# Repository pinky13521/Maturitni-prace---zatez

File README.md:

# ⚡ Programovatelná stejnosměrná elektronická zátěž (0–30 V / 0–5 A / 65 W)

-green?style=flat-square&logo=kicad)

**Maturitní projekt** na SPŠ elektrotechnické zaměřený na návrh, konstrukci a programové vybavení číslicově řízené laboratorní stejnosměrné elektronické zátěže. Zařízení slouží k testování charakteristik napájecích zdrojů, ověřování proudové zatížitelnosti adaptérů a automatizovanému měření kapacity i vnitřního odporu akumulátorů.

---

## 🎯 Hlavní technické parametry

| Parametr | Hodnota / Rozsah | Poznámka |
| :--- | :--- | :--- |
| **Vstupní napětí ($U_{\text{in}}$)** | **0 – 30 V DC** | Havarijní přepěťová ochrana OVP při 32,0 V (kritická 34,0 V) |
| **Zatěžovací proud ($I_{\text{load}}$)** | **0 – 5,0 A** | Nadproudová ochrana OCP při 5,20 A |
| **Maximální ztrátový výkon ($P_{\text{max}}$)** | **65 W trvale** (100 W špičkově) | Aktivní chlazení CPU chladičem s heatpipes + softwarový derating |
| **Rozlišení nastavení proudu (DAC)** | **~1,22 mA / LSB** | Externí 12-bitový I2C D/A převodník **MCP4725** |
| **Rozlišení měření (ADC)** | **1,38 mV / 1,25 mA** | Externí 16-bitový Sigma-Delta A/D převodník **ADS1115** (860 SPS) |
| **Provozní režimy** | **CC, CP, CR, BATT** | Konstantní proud, výkon, odpor a automatický test baterií |
| **Regulační smyčka** | **Analogová + 50 Hz digitální** | Plynulý soft-start náběh proudu (17,5 A/s) bez rázů |
| **Ovládání a rozhraní** | **OLED + Enkodér + Wi-Fi Web** | Lokální 0,96" OLED displej, rotační enkodér s akcelerací, Web HUD |

---

## 🛠️ Hybridní architektura systému

Zařízení využívá **hybridní analogově-digitální koncepci**, která spojuje bleskovou odezvu analogového regulátoru s přesností a inteligencí mikrokontroléru ESP32:

```mermaid
flowchart LR
    subgraph Power["Výkonová a analogová část"]
        DUT["Testovaný zdroj / Baterie\n(0–30 V / 0–5 A)"] --> Q1["IRFP250N\n(TO-247 MOSFET)"]
        Q1 --> RSH["Bočník 0,100 Ω / 10 W\n(4-vodičové Kelvinovo snímání)"]
        RSH --> GND["GND"]
        DAC["MCP4725\n(12-bit DAC)"] --> OA["LM358\n(Operační zesilovač)"]
        RSH -. "Zpětná vazba IMON" .-> OA
        OA -- "Buzení Gate" --> Q1
    end

    subgraph Digital["Číslicové řízení a telemetrie (ESP32)"]
        ADC["ADS1115\n(16-bit ADC)"] --> ESP["ESP32 DevKit V1\n(240 MHz Dual-Core)"]
        DUT -. "Dělič 1:11 (VMON)" .-> ADC
        RSH -. "Úbytek (IMON)" .-> ADC
        TEMP["DS18B20\n(Teplota chladiče)"] --> ESP
        ENC["Rotační enkodér\nKY-040"] --> ESP
        ESP --> DAC
        ESP -- "25 kHz PWM" --> FAN["4-pin PC Ventilátor"]
        ESP --> OLED["0.96\" SSD1306 OLED"]
        ESP <--> WEB["Wi-Fi Webové Rozhraní\n(http://zatez.local)"]
    end
```

1. **Rychlá analogová proudová smyčka**: Operační zesilovač **LM358** plynule porovnává žádané napětí z D/A převodníku s okamžitým úbytkem napětí na výkonovém bočníku **0,100 Ω / 10 W** a řídí hradlo výkonového N-MOSFETu **IRFP250N** v lineárním režimu. Analogová smyčka reaguje v řádu mikrosekund a potlačuje proudové špičky při připojení zátěže.
2. **Číslicový dohled a regulace (ESP32)**: Mikrokontrolér v deterministické 50Hz smyčce (perioda 20 ms) čte skutečné svorkové napětí a proud pomocí 16-bitového **ADS1115**, přepočítává požadovaný proud pro režimy **CP** ($I = P/U$), **CR** ($I = U/R$) a **BATT**, integruje kapacitu ($\text{mAh}, \text{Wh}$) a dohlíží na bezpečnostní limity.

---

## 💻 Webové rozhraní (Web Dashboard HUD)

Webová aplikace běží přímo z paměti PROGMEM mikrokontroléru ESP32 (dostupná v lokální síti přes mDNS na adrese `http://zatez.local` nebo v záložním AP režimu `ESP32-Elektronicka-Zatez`).

### Klíčové funkce webového rozhraní:
* **☰ Vysouvací postranní panel (GitHub-style Drawer Menu)**: Kliknutím na ikonu tří čárek `☰` v levém horním rohu se vysune přehledné navigační menu rozdělené do sekcí (*Provoz a měření*, *Konfigurace a systém*, *Vzhled a rozhraní*) včetně živého mini-přehledu veličin a rychlého přepínače motivů.
* **📊 4 barevně kódované digitální přístroje**:
  * ⚡ **Napětí ($U$)**: Ledově modrá (`0.00 V`)
  * 🟢 **Proud ($I$)**: Smaragdově zelená (`0.000 A`)
  * 🟡 **Výkon ($P$)**: Jantarově zlatá (`0.0 W`)
  * 🔴 **Teplota & Ventilátor ($T$)**: Korálově červená (`25.0 °C // 20%`)
* **📈 Retina HiDPI osciloskop**: Vykreslování průběhu napětí a proudu v reálném čase s automatickým škálováním podle `window.devicePixelRatio`, volbou délky paměti (`50 / 100 / 150` bodů) a přepínáním **lineárního (LIN)** i **logaritmického (LOG)** měřítka osy Y i posuvníku.
* **🔋 Analyzátor kapacity baterií**:
  * Přesné měření vybíjecí kapacity v **mAh / Ah** a energie ve **Wh** (64-bitová integrace).
  * Automatický výpočet **vnitřního odporu článku ($R_i$)** v $\text{m}\Omega$ metodou poklesu napětí při zatížení ($R_i = \Delta U / \Delta I$).
  * Rychlé předvolby pro **Li-Ion / LiPo (3,0 V)**, **LiFePO4 (2,5 V)**, **NiMH (1,0 V)** a **Pb 12V (10,5 V)** s automatickým odpojením při dosažení mezního napětí (Cut-off).
* **📥 Záznamník dat (Data Logger) a export**:
  * Záznam průběhu měření do paměti s přímým exportem do **Excelu (`.csv` s UTF-8 BOM a českým formátem desetinné čárky)**, surového **`.json`** a uložením snímku grafu jako **`.png` obrázku**.
* **🎨 5 laboratorních barevných motivů & lokalizace**:
  * *Cyber Dark*, *Keithley Amber*, *CRT Phosphor Green*, *Neon Cyan* a *Clean Paper Light* (světlý režim pro tisk do protokolů).
  * Okamžité přepínání jazyka **Čeština (CZ) / English (EN)** a zvuková odezva tlačítek i alarmů přes **Web Audio API**.

---

## ⚡ Optimalizace firmwaru (v2.5 Optimized Pro)

1. **Ne-blokující asynchronní stavový automat ADC (`adc_driver.cpp`)**:
   * Odstraněno blokující čekání na I2C převody. Stavový automat `poll()` spouští převody na pozadí (860 SPS) a střídá kanály napětí a proudu. Samotné čtení v regulační smyčce trvá **0 µs**.
2. **Plynulý Soft-Start náběh proudu (`dac_driver.cpp`)**:
   * Implementován omezovač strmosti náběhu (*slew-rate limiter* max. $+0{,}35\,\text{A} / 20\,\text{ms} = 17{,}5\,\text{A/s}$), který chrání testovaný zdroj i MOSFET před proudovými rázy a překmity. Vypnutí zátěže zůstává okamžité.
3. **Dynamická akcelerace rotačního enkodéru (`encoder_driver.cpp`)**:
   * Přerušovací rutina měří rychlost otáčení knoflíku ($\Delta t$ v $\mu\text{s}$). Při pomalém otáčení umožňuje jemné krokování po 50 mA ($1\times$), při rychlém protočení násobí krok ($2\times$ až $3\times$).
4. **64-bitová integrace kapacity (`load_regulator.cpp`)**:
   * Vnitřní akumulátory mAh a Wh využívají 64-bitový typ `double`, čímž eliminují zaokrouhlovací chybu plovoucí řádové čárky při dlouhodobých vícehodinových testech baterií.
5. **Odolnost bezpečnostních ochran proti šumu (`safety.cpp`)**:
   * Čtyřstupňový **Safety Supervisor** (**OVP** 32 V, **OCP** 5,2 A, **OPP** 65 W, **OTP** 75 °C) využívá persistenciální filtr (potvrzení 2–3 po sobě jdoucích vzorků za 40–60 ms) proti falešným sepnutím vlivem rušení, zatímco při kritickém přepětí ($>34\,\text{V}$) odpojuje zátěž okamžitě.
6. **Optimalizace Flash paměti (`min_spiffs.csv` + `-O2`)**:
   * Úpravou rozvržení partition tabulky a kompilační optimalizací `-O2` bylo využití paměti Flash sníženo z 94 % na **56,8 %**.

---

## 📌 Přiřazení pinů ESP32 (Pinout dle schématu v KiCadu)

| Periferie / Signál | Pin ESP32 (GPIO) | Konektor na DPS | Popis funkce |
| :--- | :--- | :--- | :--- |
| **I2C SDA** | `GPIO 26` | `J_ESP_R1` (pin 7) | Datová linka I2C (400 kHz Fast Mode – OLED, ADS1115, MCP4725) |
| **I2C SCL** | `GPIO 14` | `J_ESP_R1` (pin 5) | Hodinová linka I2C (400 kHz) |
| **1-Wire DS18B20** | `GPIO 32` | `J_ESP_R1` (pin 10) | Digitální teploměr chladiče Dallas DS18B20 (4,7 kΩ pull-up) |
| **PWM Ventilátor** | `GPIO 33` | `J_ESP_R1` (pin 9) | 25 kHz PWM řízení otáček 4-pinového PC ventilátoru (20–100 %) |
| **Enkodér CLK** | `GPIO 18` | `J_ESP_L1` (pin 9) | Externí přerušení rotačního enkodéru (kanál A) |
| **Enkodér DT** | `GPIO 19` | `J_ESP_L1` (pin 10) | Směrový signál rotačního enkodéru (kanál B) |
| **Enkodér SW** | `GPIO 21` | `J_ESP_L1` (pin 11) | Tlačítko enkodéru (krátký stisk = ZAP/VYP, dlouhý stisk = změna režimu) |

---

## 📁 Struktura repozitáře

```text
├── hardware/                  # Kompletní návrh DPS a schématu v KiCad 9.0
│   ├── elektronicka zatez.kicad_pro
│   ├── elektronicka zatez.kicad_sch   # Elektrické schéma (32 součástek, plně propojeno)
│   └── elektronicka zatez.kicad_pcb   # Dvouvrstvá DPS (DRC: 0 chyb, 0 nepřipojených spojů)
├── firmware/                  # Zdrojový kód pro ESP32 (PlatformIO / Arduino C++)
│   ├── platformio.ini         # Konfigurace sestavení, knihoven a partition tabulky
│   ├── include/
│   │   ├── config.h           # Konfigurace pinů, kalibrace, Wi-Fi a bezpečnostních limitů
│   │   ├── types.h            # Datové struktury a výčtové typy
│   │   ├── hal/               # Ovladače hardwaru (ADC, DAC, Ventilátor, Teploměr, Enkodér)
│   │   ├── core/              # Regulační smyčka (CC/CP/CR/BATT) a Safety Supervisor
│   │   ├── ui/                # Vykreslování na 0,96" OLED displej SSD1306
│   │   └── net/               # Wi-Fi manažer, REST API server a Web Dashboard (PROGMEM)
│   └── src/                   # Implementační soubory (.cpp) a hlavní smyčka main.cpp
└── docs/                      # Technická dokumentace a kusovník (BOM)
```

---

## 🚀 Kompilace a nahrání firmwaru

1. Otevřete složku `firmware/` ve vývojovém prostředí **VS Code** s rozšířením **PlatformIO**.
2. V souboru [`firmware/include/config.h`](firmware/include/config.h) můžete upravit přihlašovací údaje k domácí Wi-Fi síti (`WIFI_STA_SSID` a `WIFI_STA_PASS`). Pokud se zátěž k routeru nepřipojí, automaticky vytvoří vlastní přístupový bod **`ESP32-Elektronicka-Zatez`** (heslo `12345678`, IP `192.168.4.1`).
3. Zkompilujte a nahrajte projekt příkazem:
   ```bash
   pio run -t upload -d firmware
   ```
4. Otevřete webové rozhraní v prohlížeči na adrese **`http://zatez.local`** (nebo na IP adrese vypsané na OLED displeji při startu).

---
*Autor projektu: **Ondřej Pinkas** — Maturitní práce, SPŠ Elektrotechnická*

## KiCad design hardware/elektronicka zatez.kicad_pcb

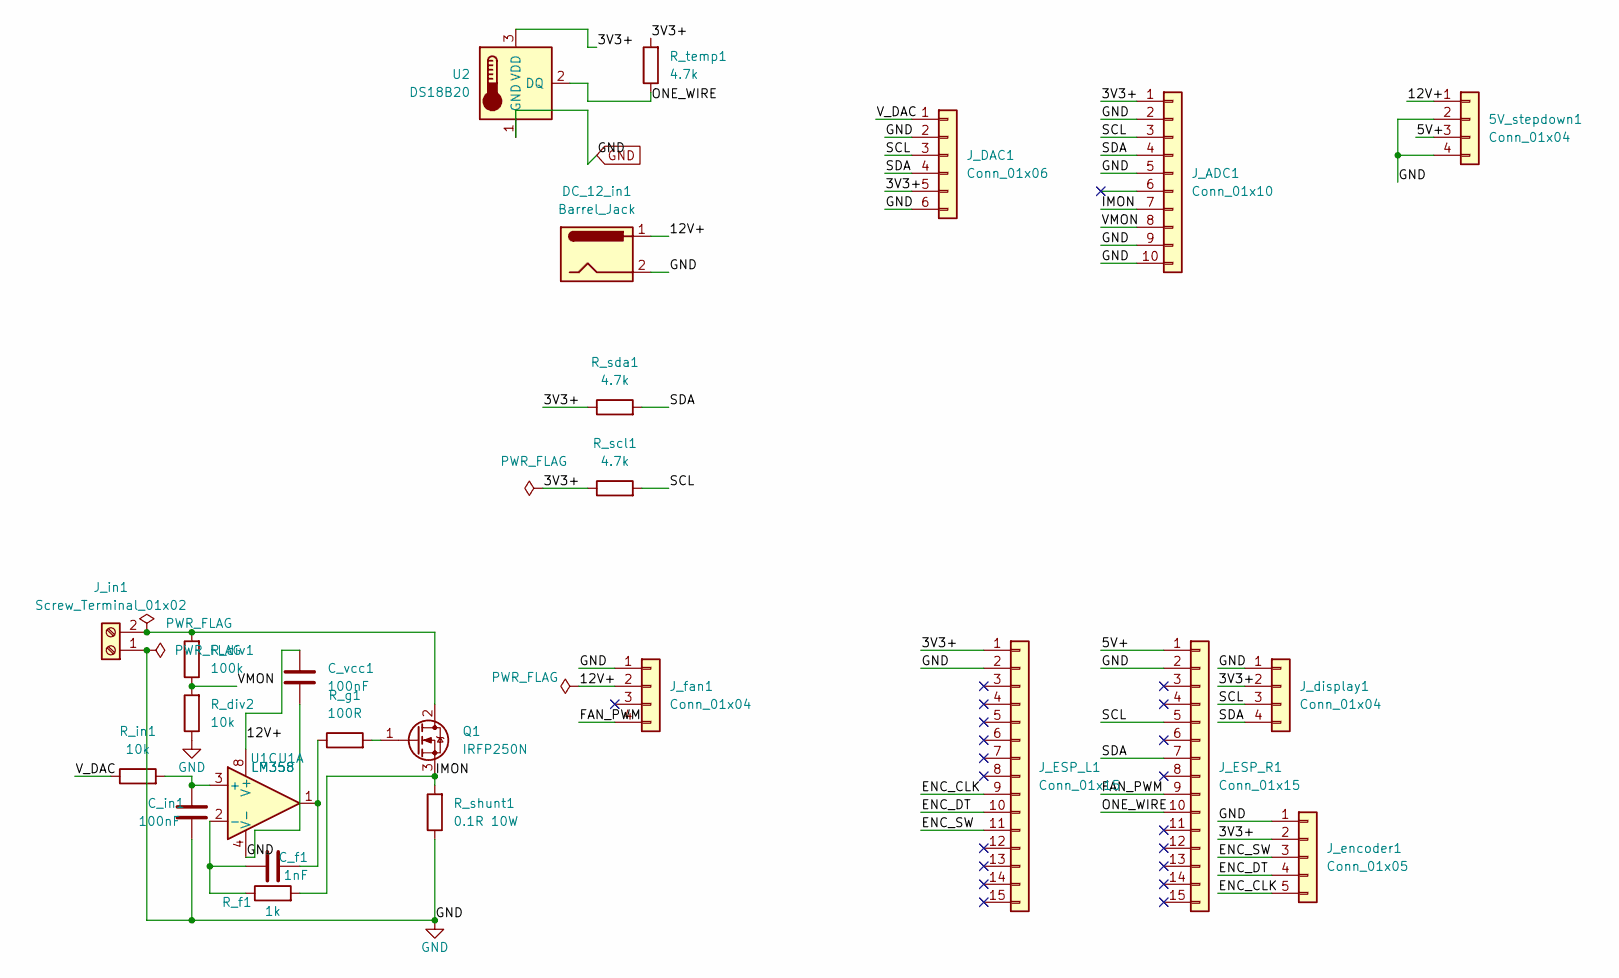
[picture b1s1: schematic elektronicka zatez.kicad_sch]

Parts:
5V_stepdown1: Conn_01x04; PinHeader_1x04_P2.54mm_Vertical
C_f1: 1nF; C_Disc_D5.0mm_W2.5mm_P5.00mm
C_in1: 100nF; C_Disc_D5.0mm_W2.5mm_P5.00mm
C_vcc1: 100nF; C_Disc_D5.0mm_W2.5mm_P5.00mm
DC_12_in1: Barrel_Jack; BarrelJack_CUI_PJ-063AH_Horizontal
J_ADC1: Conn_01x10; PinSocket_1x10_P2.54mm_Vertical
J_DAC1: Conn_01x06; PinSocket_1x06_P2.54mm_Vertical
J_ESP_L1: Conn_01x15; PinSocket_1x15_P2.54mm_Vertical
J_ESP_R1: Conn_01x15; PinSocket_1x15_P2.54mm_Vertical
J_display1: Conn_01x04; PinSocket_1x04_P2.54mm_Vertical
J_encoder1: Conn_01x05; PinHeader_1x05_P2.54mm_Vertical
J_fan1: Conn_01x04; PinSocket_1x04_P2.54mm_Vertical
J_in1: Screw_Terminal_01x02; TerminalBlock_Phoenix_MKDS-1,5-2-5.08_1x02_P5.08mm_Horizont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
Q1: IRFP250N; TO-247-3_Vertical
R_div1: 100k; R_Axial_DIN0207_L6.3mm_D2.5mm_P10.16mm_Horizontal
R_div2: 10k; R_Axial_DIN0207_L6.3mm_D2.5mm_P10.16mm_Horizontal
R_f1: 1k; R_Axial_DIN0207_L6.3mm_D2.5mm_P10.16mm_Horizontal
R_g1: 100R; R_Axial_DIN0207_L6.3mm_D2.5mm_P10.16mm_Horizontal
R_in1: 10k; R_Axial_DIN0207_L6.3mm_D2.5mm_P10.16mm_Horizontal
R_scl1: 4.7k; R_Axial_DIN0207_L6.3mm_D2.5mm_P10.16mm_Horizontal
R_sda1: 4.7k; R_Axial_DIN0207_L6.3mm_D2.5mm_P10.16mm_Horizontal
R_shunt1: 0.1R 10W; R_Axial_Power_L50.0mm_W9.0mm_P55.88mm
R_temp1: 4.7k; R_Axial_DIN0207_L6.3mm_D2.5mm_P10.16mm_Horizontal
U1: LM358; DIP-8_W7.62mm
U2: DS18B20; TO-92_Inline

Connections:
/3V3+: J_ADC1.1, J_DAC1.5, J_ESP_L1.1, J_display1.2, J_encoder1.2, R_scl1.1, R_sda1.1, R_temp1.2, U2.3 (VDD); also elsewhere on the board
/5V+: 5V_stepdown1.3, J_ESP_R1.1
/12V+: 5V_stepdown1.1, C_vcc1.1, DC_12_in1.1, J_fan1.2, U1.8 (V+)
/ENC_CLK: J_ESP_L1.9, J_encoder1.5
/ENC_DT: J_ESP_L1.10, J_encoder1.4
/ENC_SW: J_ESP_L1.11, J_encoder1.3
/FAN_PWM: J_ESP_R1.9, J_fan1.4
/IMON: J_ADC1.7, Q1.3 (S), R_f1.2, R_shunt1.2
/ONE_WIRE: J_ESP_R1.10, R_temp1.1, U2.2 (DQ); also elsewhere on the board
/SCL: J_ADC1.3, J_DAC1.3, J_ESP_R1.5, J_display1.3, R_scl1.2
/SDA: J_ADC1.4, J_DAC1.4, J_ESP_R1.7, J_display1.4, R_sda1.2
/VMON: J_ADC1.8, R_div1.1, R_div2.2
/V_DAC: J_DAC1.1, R_in1.1
GND: 5V_stepdown1.2, 5V_stepdown1.4, C_in1.2, C_vcc1.2, DC_12_in1.2, J_ADC1.2, J_ADC1.5, J_ADC1.9, J_ADC1.10, J_DAC1.2, J_DAC1.6, J_ESP_L1.2, J_ESP_R1.2, J_display1.1, J_encoder1.1, J_fan1.1, J_in1.1, R_div2.1, R_shunt1.1, U1.4 (V-), U2.1 (GND); also elsewhere on the board
unnamed: C_f1.1, R_g1.1, U1.1
unnamed: C_f1.2, R_f1.1, U1.2 (-)
unnamed: C_in1.1, R_in1.2, U1.3 (+)
unnamed: J_in1.2, Q1.2 (D), R_div1.2
unnamed: Q1.1 (G), R_g1.2

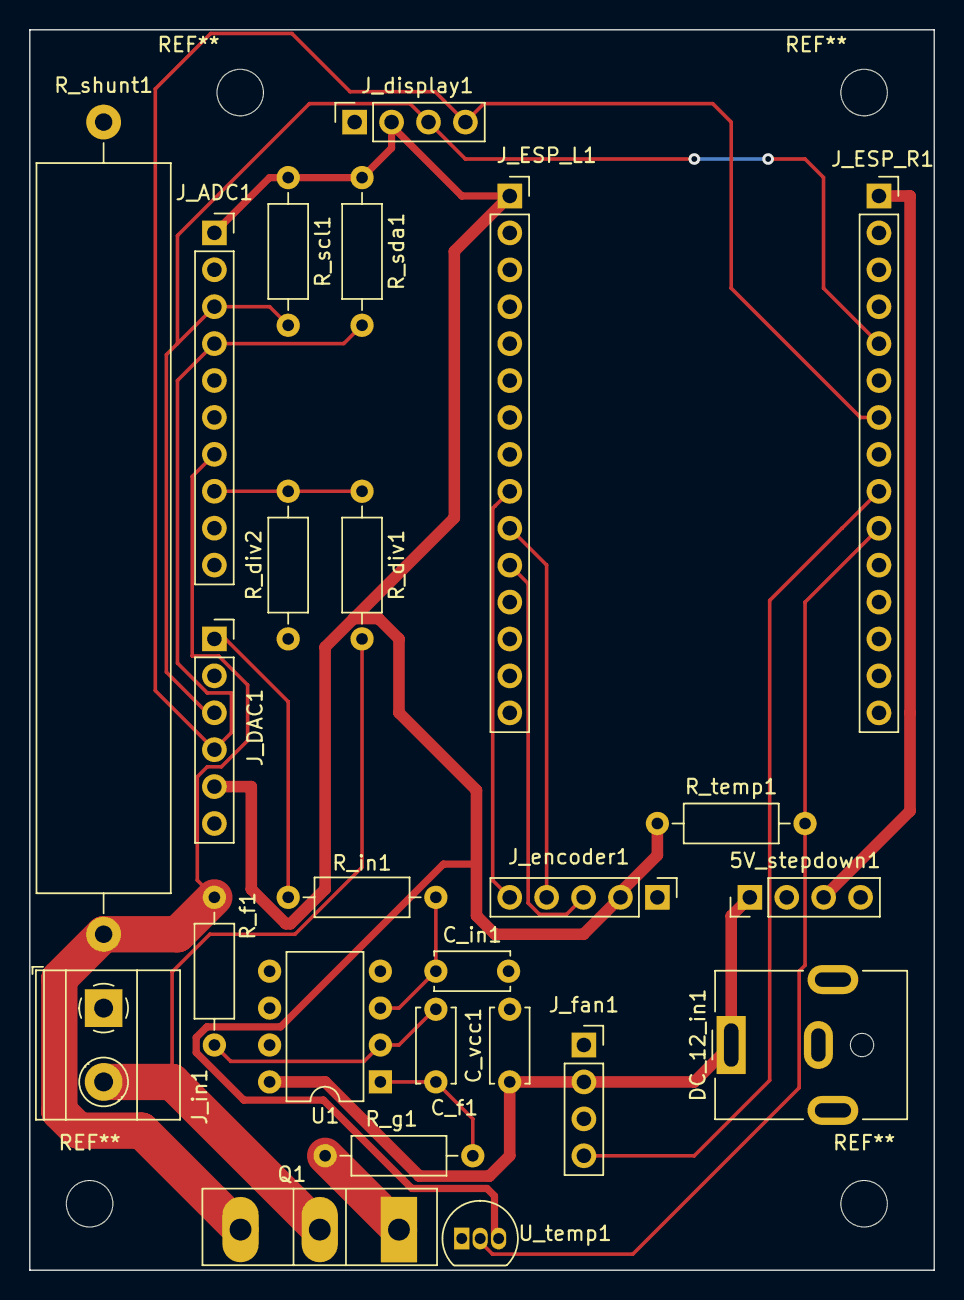
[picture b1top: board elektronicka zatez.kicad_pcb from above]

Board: 2 copper layers, 62.2 x 85.3 mm, 25 parts (0 on the bottom side), 19 nets.

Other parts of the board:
U_temp1: DS18B20; TO-92_Inline

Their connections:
/3V3+: U_temp1.3 (VDD); also elsewhere on the board
/ONE_WIRE: U_temp1.2 (DQ); also elsewhere on the board
GND: U_temp1.1 (GND); also elsewhere on the board

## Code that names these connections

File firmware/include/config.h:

/**
 * @file config.h
 * @brief Konfigurace pinů, kalibračních konstant a bezpečnostních limitů
 * @project Programovatelná stejnosměrná elektronická zátěž
 * @author Ondřej Pinkas
 */

#ifndef CONFIG_H
#define CONFIG_H

#include <Arduino.h>

// =============================================================================
// 1. PŘIŘAZENÍ PINŮ (Dle KiCad schématu pro ESP32 DevKit V1 30-pin)
// =============================================================================

// I2C Sběrnice (OLED 128x64, ADS1115, MCP4725) - ESP32 USB-C konektorem nahoru
#define PIN_I2C_SDA 26  // J_ESP_R1 pin 7 (GPIO26 / D26)
#define PIN_I2C_SCL 14  // J_ESP_R1 pin 5 (GPIO14 / D14)
#define I2C_FREQ 400000 // 400 kHz (Fast Mode)

// I2C Adresy modulů
#define I2C_ADDR_OLED 0x3C    // Výchozí adresa 0.96" SSD1306 displeje
#define I2C_ADDR_ADS1115 0x48 // Výchozí adresa 16-bit ADC (ADDR -> GND)
#define I2C_ADDR_MCP4725 0x60 // Výchozí adresa 12-bit DAC (A0 -> GND)

// Kanály ADS1115 (Dle KiCad schématu: J_ADC1 pin 7 = A0 -> IMON, pin 8 = A1 ->
// VMON)
#define ADC_CHANNEL_IMON 0 // Kanál A0: Snímání proudu bočníkem (IMON)
#define ADC_CHANNEL_VMON 1 // Kanál A1: Snímání napětí děličem (VMON)

// Rotační enkodér s tlačítkem
#define PIN_ENC_CLK 18 // J_ESP_L1 pin 9 (GPIO18 / D18)
#define PIN_ENC_DT 19  // J_ESP_L1 pin 10 (GPIO19 / D19)
#define PIN_ENC_SW 21  // J_ESP_L1 pin 11 (GPIO21 / D21)

// PWM řízení 4pinového ventilátoru
#define PIN_FAN_PWM 33     // J_ESP_R1 pin 9 (GPIO33 / D33)
#define FAN_PWM_CHANNEL 0  // LEDC kanál (pro Core 2.x)
#define FAN_PWM_FREQ 25000 // 25 kHz (standard pro 4-pin PC ventilátory)
#define FAN_PWM_RES 8      // 8-bitové rozlišení (0 až 255)

// 1-Wire sběrnice pro teplotní senzor Dallas DS18B20
#define PIN_ONE_WIRE 32 // J_ESP_R1 pin 10 (GPIO32 / D32)

#define SERIAL_DEBUG 1 // 1 = ladicí výpisy do Serial monitoru, 0 = vypnuto

#if SERIAL_DEBUG
#define LOG_PRINTLN(x) Serial.println(x)
#define LOG_PRINTF(...) Serial.printf(__VA_ARGS__)
#define LOG_PRINT(x) Serial.print(x)
#else
#define LOG_PRINTLN(x)
#define LOG_PRINTF(...)
#define LOG_PRINT(x)
#endif

// =============================================================================
// 2. HARDWAROVÉ A KALIBRAČNÍ KONSTANTY
// =============================================================================

// Proudový bočník (R_shunt1 = 0.1 Ohm / 10W Kelvinovo čtyřvodičové zapojení)
#define SHUNT_RESISTANCE_OHM 0.100f

// Napěťový dělič vstupu (R_div1 = 100k, R_div2 = 10k) => poměr (100+10)/10
// = 11.0
#define VOLTAGE_DIVIDER_RATIO 11.00f

// D/A Převodník MCP4725 (12-bit: 0..4095)
#define DAC_VREF_VOLTS 3.300f // Skutečná napájecí větev 3.3V
#define DAC_MAX_VALUE 4095

// =============================================================================
// 3. BEZPEČNOSTNÍ LIMITY (SAFETY SUPERVISOR)
// =============================================================================

#define LIMIT_MAX_VOLTAGE 32.0f // [V] OVP - Přepěťová ochrana
#define LIMIT_MAX_CURRENT 5.2f  // [A] OCP - Nadproudová ochrana
#define LIMIT_MAX_POWER 65.0f   // [W] OPP - Maximální ztrátový výkon
#define LIMIT_MAX_TEMP 75.0f    // [°C] OTP - Havarijní vypnutí zátěže
#define LIMIT_WARN_TEMP 65.0f   // [°C] Výstražná teplota (ventilátor 100%)

// Křivka ventilátoru
#define TEMP_FAN_MIN 32.0f // [°C] Pod touto teplotou minimální otáčky (20%)
#define TEMP_FAN_MAX 60.0f // [°C] Nad touto teplotou plné otáčky (100%)

// =============================================================================
// 4. WI-FI A WEBOVÝ SERVER
// =============================================================================

// Režim Klienta (STA) - ESP32 se připojí k vaší domácí / školní Wi-Fi síti nebo
// hotspotu. Skutečné údaje uložte do souboru include/secrets.h (viz secrets.h.example),
// který je v .gitignore a nenahrává se na GitHub:
#if __has_include("secrets.h")
  #include "secrets.h"
#else
  #define WIFI_STA_SSID "Vase-WiFi-Nazev"  // Zadejte název své Wi-Fi sítě
  #define WIFI_STA_PASS "Vase-WiFi-Heslo"  // Zadejte heslo k Wi-Fi
#endif
#define WIFI_STA_TIMEOUT_MS 9000 // Časový limit pro připojení k routeru [ms]

// Záložní režim Access Point (AP) - Spustí se automaticky, pokud se nepodaří
// připojit k STA:
#define WIFI_AP_SSID "ESP32-Elektronicka-Zatez"
#define WIFI_AP_PASS "12345678"
#define WEB_SERVER_PORT 80

// Lokální mDNS adresa - V prohlížeči otevřete přímo: http://zatez.local
#define MDNS_HOSTNAME "zatez"

// =============================================================================
// 5. MQTT PROPOJENÍ S LOKÁLNÍM SERVEREM (VOLITELNÉ)
// =============================================================================
// Přepněte na 1, jakmile rozchodíte Mosquitto broker na vašem serveru.
// Při 0 běží pouze vestavěný lokální webový server na ESP32.
#define MQTT_ENABLED             0
#define MQTT_BROKER_IP           "192.168.31.251"
#define MQTT_BROKER_PORT         1883
#define MQTT_CLIENT_ID           "esp32-zatez"
#define MQTT_PUBLISH_INTERVAL_MS 200
#define MQTT_TOPIC_TELEMETRY     "zatez/telemetry"
#define MQTT_TOPIC_CONTROL       "zatez/control"
#define MQTT_TOPIC_STATUS        "zatez/status"

#endif // CONFIG_H
